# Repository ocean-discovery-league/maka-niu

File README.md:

# maka-niu

"Maka" - Eye, "Niu" - Coconut

Maka Niu, aka the "CocoCam,"  is a low-cost oceanographic camera and sensor platform that enables the exploration of undersea environments using a new pressure-tolerant camera housing and an all-natural, locally sourced, biodegradable buoyancy-control device. The coconut (Cocos nucifera ) can float for over 3,000 miles and still remain viable; as such, it makes an excellent organic platform for deploying scientific apparatus.

Maka Niu is a community-driven project that allows local groups to explore and monitor their marine resources. Based around off-the-shelf single-board computers and readily available microprocessors, Maka Niu is inexpensive to produce, easy to program, and simple to use. Designed as an open platform for scientific education and exploration, it will give classrooms and communities the ability to upload video and sensor data into FathomNet, a centralized database where machine learning algorithms assist with classification of marine species, seabed substrate identification, and accumulated time-series sensor data. This data will be publically available, allowing visualization, sharing, and discussion with policy makers from the local to global levels.

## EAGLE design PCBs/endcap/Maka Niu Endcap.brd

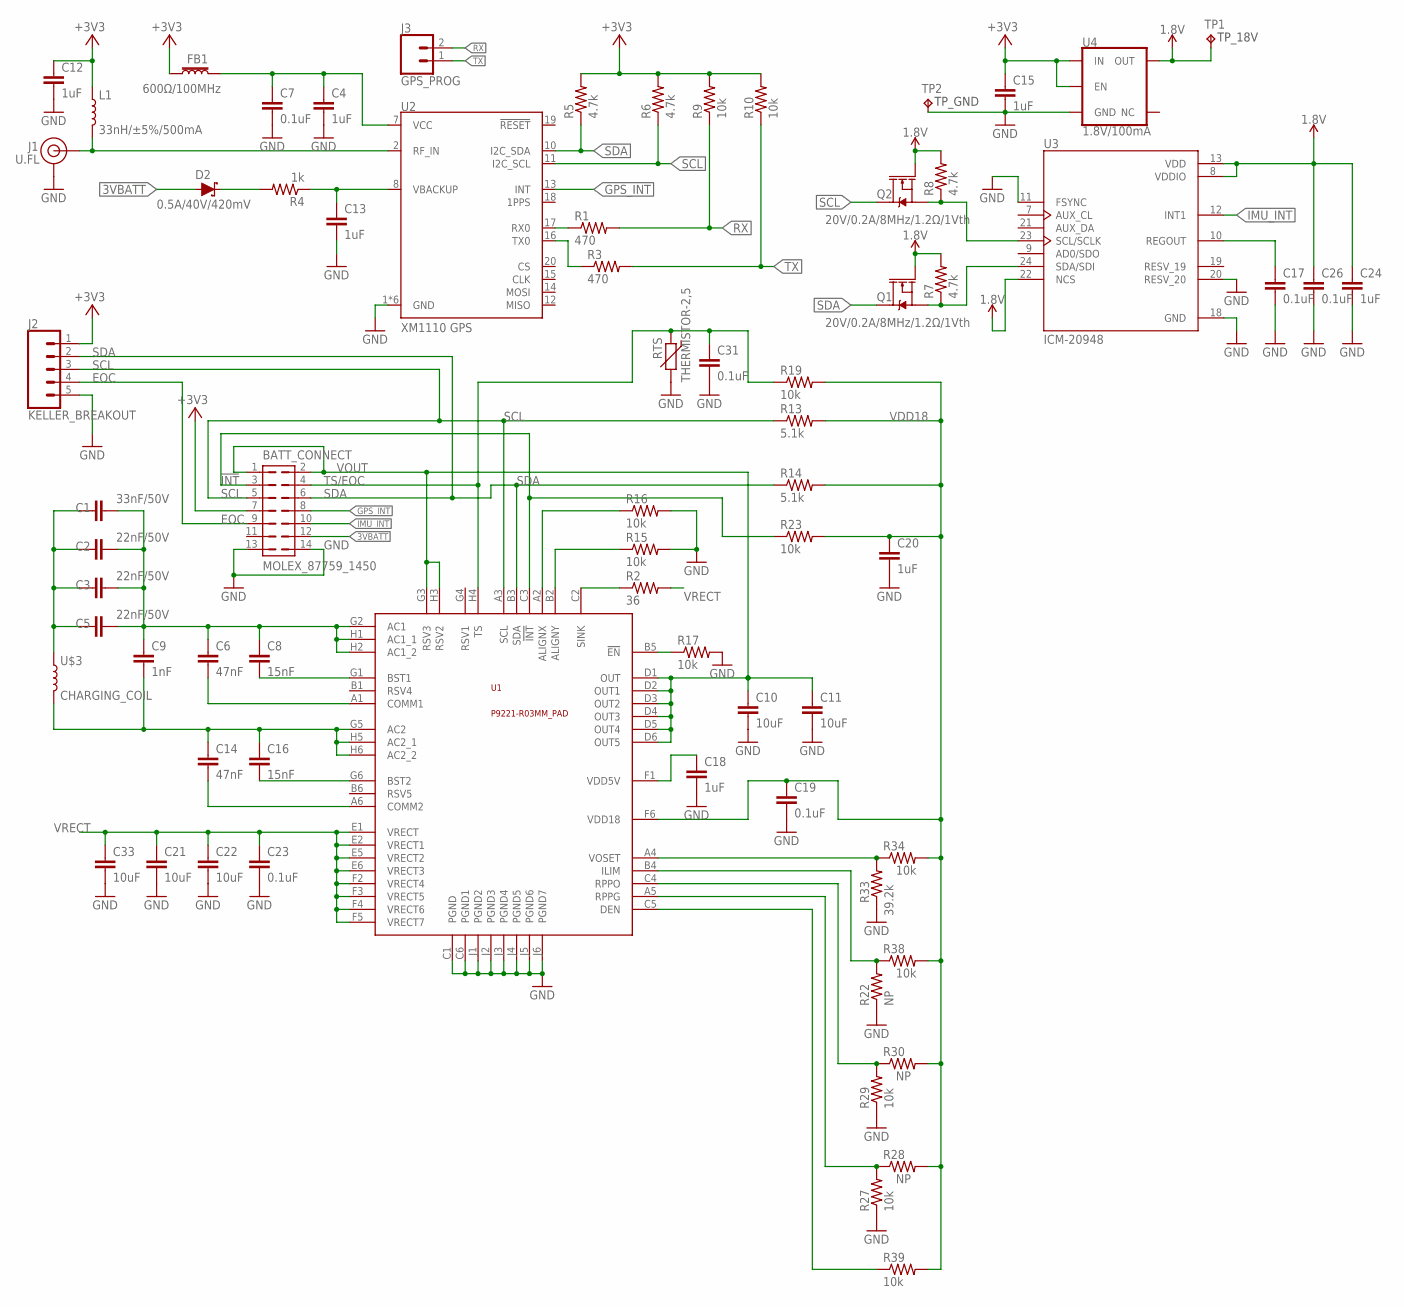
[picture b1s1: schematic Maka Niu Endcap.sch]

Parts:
BATT_CONNECT: MOLEX_87759_1450; 87759-1450; DIGI-KEY_PART_NUMBER WM18654-ND
C1: 33nF/50V; C0402; DIGI-KEY_PART_NUMBER 490-13296-1-ND
C2, C3, C5: 22nF/50V; C0402; DIGI-KEY_PART_NUMBER 490-6360-1-ND
C4, C12, C13, C15, C18, C20, C24: 1uF; C0402; DIGI-KEY_PART_NUMBER 311-1439-1-ND
C6, C14: 47nF; C0402; DIGI-KEY_PART_NUMBER 490-10702-1-ND
C7, C17, C26: 0.1uF; C0402; DIGI-KEY_PART_NUMBER 490-11917-1-ND
C8, C16: 15nF; C0402; DIGI-KEY_PART_NUMBER 490-16428-1-ND
C9: 1nF; C0402; DIGI-KEY_PART_NUMBER 732-7556-1-ND
C10, C11, C21, C22, C33: 10uF; C_0603; DIGI-KEY_PART_NUMBER 445-9015-1-ND
C19, C31: 0.1uF; C0201; DIGI-KEY_PART_NUMBER 445-7318-1-ND
C23: 0.1uF; C0201; DIGI-KEY_PART_NUMBER 1276-1318-1-ND
D2: 0.5A/40V/420mV; SOD-323; DIGI-KEY_PART_NUMBER 1727-5209-1-ND
FB1: 600Ω/100MHz; 0603; DIGI-KEY_PART_NUMBER 445-172898-1-ND
J1: U.FL; DIGI-KEY_PART_NUMBER A144746CT-ND
J2: KELLER_BREAKOUT; WIRES_2MM_05
J3: GPS_PROG; WIRES_2MM_02SMD
L1: 33nH/±5%/500mA; 0603; DIGI-KEY_PART_NUMBER 490-14837-1-ND
Q1, Q2: 20V/0.2A/8MHz/1.2Ω/1Vth; SOT-416FL; DIGI-KEY_PART_NUMBER RE1C002UNTCLCT-ND
R1, R3: 470; R0402; DIGI-KEY_PART_NUMBER RMCF0402JT470RCT-ND
R2: 36; R0805; DIGI-KEY_PART_NUMBER P36ADCT-ND
R4: 1k; R0402; DIGI-KEY_PART_NUMBER RMCF0402JT1K00CT-ND
R5, R6, R7, R8: 4.7k; R0402; DIGI-KEY_PART_NUMBER RMCF0402JT4K70CT-ND
R9, R10: 10k; R0402; DIGI-KEY_PART_NUMBER RMCF0402JT10K0CT-ND
R13, R14: 5.1k; R0402; DIGI-KEY_PART_NUMBER CR0402-JW-512GLFCT-ND
R15, R16: 10k; R_0603; DIGI-KEY_PART_NUMBER 311-10.0KHRCT-ND
R17, R19, R23, R27, R29, R34, R38, R39: 10k; R0402; DIGI-KEY_PART_NUMBER 541-10KATCT-ND
R22, R28, R30: NP; R0402
R33: 39.2k; R0402; DIGI-KEY_PART_NUMBER 311-39.2KLBCT-ND
RTS: THERMISTOR-2,5; RS-2,5
TP1: TP_18V; B1,27
TP2: TP_GND; B1,27
U1: P9221-R03MM_PAD; CSP52_2P64X3P94_0P4MM_03MMPAD; DIGI-KEY_PART_NUMBER 800-3932-2-ND
U2: XM1110 GPS; XM1110_GPS; DIGI-KEY_PART_NUMBER 1645-XM1110_1104311CT-ND
U3: ICM-20948; QFN40P300X300X105-24N
U4: 1.8V/100mA; SC70; DIGI-KEY_PART_NUMBER 576-2807-1-ND
U$3: CHARGING_COIL

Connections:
1.8V: C24.1, C26.1, Q1.1 (G), Q2.1 (G), R7.2, R8.2, TP1.TP, U3.8 (VDDIO), U3.13 (VDD), U3.22 (NCS), U4.5 (OUT)
3VBATT: BATT_CONNECT.12, D2.A
!INT: BATT_CONNECT.3, R23.1, U1.C3 (!INT)
+3V3: BATT_CONNECT.7, C12.1, C15.1, FB1.1, J2.1, L1.1, R5.2, R6.2, R9.2, R10.2, U4.1 (IN), U4.3 (EN)
AC1: C1.2, C2.2, C3.2, C5.2, C6.1, C8.1, C9.1, U1.G2 (AC1), U1.H1 (AC1_1), U1.H2 (AC1_2)
AC2: C9.2, C14.1, C16.1, U1.G5 (AC2), U1.H5 (AC2_1), U1.H6 (AC2_2), U$3.B2 (2); also elsewhere on the board
ALIGNX: R16.1, U1.A2 (ALIGNX)
ALIGNY: R15.1, U1.B2 (ALIGNY)
BST1: C8.2, U1.G1 (BST1)
BST2: C16.2, U1.G6 (BST2)
COMM1: C6.2, U1.A1 (COMM1)
COMM2: C14.2, U1.A6 (COMM2)
DEN: R39.1, U1.C5 (DEN)
EOC: BATT_CONNECT.9, J2.4
GND: BATT_CONNECT.13, BATT_CONNECT.14, C4.2, C7.2, C10.2, C11.2, C12.2, C13.2, C15.2, C17.2, C18.2, C19.2, C20.2, C21.2, C22.2, C23.2, C24.2, C26.2, C31.2, C33.2, J1.1 (GND), J1.2 (GND), J2.5, R15.2, R16.2, R17.2, R22.1, R27.1, R29.1, R33.1, RTS.2, TP2.TP, U1.C1 (PGND), U1.C6 (PGND1), U1.J1 (PGND2), U1.J2 (PGND3), U1.J3 (PGND4), U1.J4 (PGND5), U1.J5 (PGND6), U1.J6 (PGND7), U2.1 (GND), U2.3 (GND), U2.4 (GND), U2.5 (GND), U2.6 (GND), U2.9 (GND), U3.11 (FSYNC), U3.18 (GND), U3.20 (RESV_20), U4.2 (GND)
GPS_INT: BATT_CONNECT.8, U2.13 (INT)
ILIM: R22.2, R38.1, U1.B4 (ILIM)
IMU_INT: BATT_CONNECT.10, U3.12 (INT1)
LC: C1.1, C2.1, C3.1, C5.1, U$3.B1 (1); also elsewhere on the board
unnamed: R17.1, U1.B5 (!EN)
unnamed: D2.C, R4.2
REGOUT: C17.1, U3.10 (REGOUT)
RF_IN: J1.FEED (SIGNAL), L1.2, U2.2 (RF_IN)
RPPG: R27.2, R28.1, U1.A5 (RPPG)
RPPO: R29.2, R30.1, U1.C4 (RPPO)
RX: J3.2, R1.2, R9.1
RX0: R1.1, U2.17 (RX0)
SCL: BATT_CONNECT.5, J2.3, Q2.3 (D), R6.1, R13.1, U1.A3 (SCL), U2.11 (I2C_SCL)
SCL/SCLK: Q2.2 (S), R8.1, U3.23 (SCL/SCLK)
SDA: BATT_CONNECT.6, J2.2, Q1.3 (D), R5.1, R14.1, U1.B3 (SDA), U2.10 (I2C_SDA)
SDA/SDI: Q1.2 (S), R7.1, U3.24 (SDA/SDI)
SINK: R2.1, U1.C2 (SINK)
TS/EOC: BATT_CONNECT.4, C31.1, R19.1, RTS.1, U1.H4 (TS)
TX: J3.1, R3.2, R10.1
TX0: R3.1, U2.16 (TX0)
VBACKUP: C13.1, R4.1, U2.8 (VBACKUP)
VCC: C4.1, C7.1, FB1.2, U2.7 (VCC)
VDD5V: C18.1, U1.F1 (VDD5V)
VDD18: C19.1, C20.1, R13.2, R14.2, R19.2, R23.2, R28.2, R30.2, R34.2, R38.2, R39.2, U1.F6 (VDD18)
VOSET: R33.2, R34.1, U1.A4 (VOSET)
VOUT: BATT_CONNECT.1, BATT_CONNECT.2, C10.1, C11.1, U1.D1 (OUT), U1.D2 (OUT1), U1.D3 (OUT2), U1.D4 (OUT3), U1.D5 (OUT4), U1.D6 (OUT5), U1.G3 (RSV3), U1.H3 (RSV2)
VRECT: C21.1, C22.1, C23.1, C33.1, R2.2, U1.E1 (VRECT), U1.E2 (VRECT1), U1.E5 (VRECT2), U1.E6 (VRECT3), U1.F2 (VRECT4), U1.F3 (VRECT5), U1.F4 (VRECT6), U1.F5 (VRECT7)

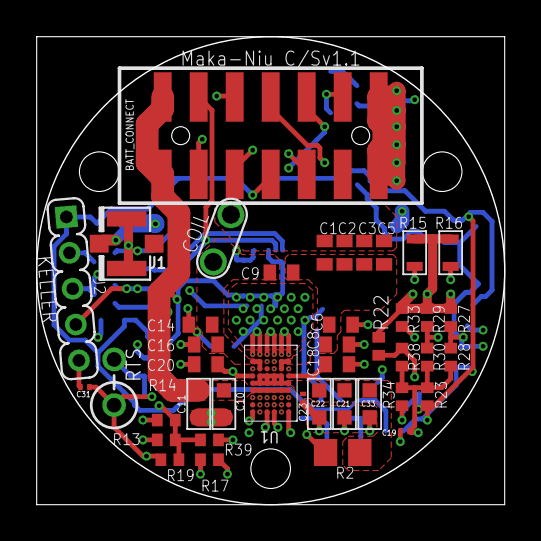
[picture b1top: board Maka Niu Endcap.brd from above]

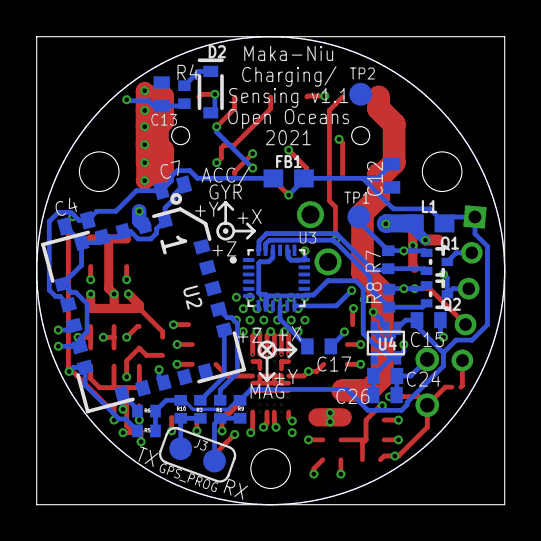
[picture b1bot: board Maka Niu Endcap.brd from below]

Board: 6 copper layers, 26.0 x 26.0 mm, 70 parts (28 on the bottom side), 42 nets.

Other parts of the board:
COIL: CHARGING_COIL

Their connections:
AC2: COIL.B2; also elsewhere on the board
LC: COIL.B1; also elsewhere on the board

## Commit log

2020-06-24 Lui's first commit, addign a python script to record video on the Pi Zero with aa camera module, with timestamp overlay. This could be used in Maka Niu to overlay temperature, depth etc. Also adding 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
2020-06-24 reorganized directory for future use
2020-07-07 Add files via upload
    Uploads a specified file to Tator
2020-07-07 Add files via upload
    Bash file to upload all mp4 files in directory (Calls TatorUpload.py with given arguments)
2020-07-13 added the kellerLD library, and a version of the example with a depth estimation based on pressure.
2020-07-17 Added a more complex python program Mode_dial_with_button for testing the the new hall sensor ring togethr with the new dial lthat incorporates a button
2020-07-31 added XM1110_example.py and supporting library. Example gets NMEA data from XM1111 via I2C and updates class objects with relevant info.
2020-08-13 Added the hall ring magnetic dial Kicad project
2020-08-13 added the battery management board kicad project
2020-08-13 Icreased trace thickness and rerouted higher freq and power paths in the battery management board
2020-08-14 added documenation folder and pushed 1st Power Distribution Chart
2020-08-14 Updated index.php: can access program.php, upload w button
2020-08-14 Updated index.php w program.php link and upload button
2020-08-14 Scaffold of page for user programmed missions
2020-08-14 added the maka niu general build BOM, and the maka niu build guide
2020-08-14 Chart of the code for program.php
    Displays all of the possible code blocks user would want to create and the respective strings for use in translating into python, and the string used to display html components
2020-08-14 changed current sensing resistor values on the BMS board to appropriately trip short and over current situations, adn to appropriately end incomig charge
2020-08-18 assigned digikey part to every item in battery management schematic, and created BOM
2020-08-31 Add files via upload
    Visual Representation and estimation calculation
2020-08-31 Add files via upload
    Documentation for Visual Representation and estimation calculations
2020-09-03 adding in progress pcb design files for the charging Station
2020-09-22 completed the wireless charger PCB design as rev 0. bom is compiled
2020-09-25 minor updating on BOM organization
2020-09-25 safety merge
2020-10-02 adding LED patterns simplified.
2020-10-22 first attempt at adding RPiCWI as a submodule
2020-10-23 added makaniu BMS board V2, and wayfinders 6cell BMS.
2020-11-22 Added haptic feedback to the Mode Dial python script
2020-11-22 updates to battery managemennt wayfinder boards, and makaniu hall sensor ring and BMS
2020-11-23 Fine of haptic feedback. new click, double click, burst, and dial change incorporated
2020-11-23 bit more fine tuning on haptic feedback. The clicks are nicer, but too hard notice by feel. Hearing them gives the illusion that they are enough, but with noise canceling headphones on, I can barely 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
2020-12-04 added comments for GPIOS
2020-12-04 Minor notes on BMS pcb project
2020-12-04 added Maka Niu User Flowchart.pdf in documentation
2020-12-07 Added a program called MakaNiu.py that begins to pull and incroporate all the peripheral hardware. Mode and button control, GPS, and image and video capture all working
2021-01-15 commented out drv vibration code because it causes crash if device not present
2021-01-18 MakaNiu.py program updated to include pressure info, as well as battery info, although it is disabled due to instability
2021-01-18 Lengthened update time for GPS and pressure to once every ten seconds, so that it interferes less with button presses. Need to bring in threads maybe, thou mixing I2c is scary. Also added a program t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
2021-01-18 improved timing interference between buttons and all the i2c time
2021-01-18 added a shell script to run python program with error log
2021-01-21 added try format to keller i2c comms to avoid occasional crash.
2021-01-22 All interfaces now protected with try/except method to prevent crashes. Program will run if any of these are missing. If all is present and talking, at startup, a green LED will hold for 3 seconds. A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
2021-01-22 added crash protection on DRV haptic feedback i2c. now Pi runs even if no interface connected.
2021-01-22 added the error log save destination on git
2021-01-25 Due to a a sepcific startup issue that emerged with introduciton of spi1, the shutdown pin has been switched with the enable endcap pin. Also added the enable endcap feature.
2021-01-26 added green light flash for GPS fix
2021-02-02 Incorporated date time from GPS. Required some changes in the gps libraries.
2021-02-02 Add files via upload
    Silkscreen modified for production
2021-02-02 Add files via upload
    Updated silkscreens
2021-02-02 Add files via upload
    Finalized for production
2021-02-02 Add files via upload
    added documentation for endcap PCB
2021-02-02 incorporated ability to name image files
2021-02-04 sped up shut down sequence
2021-02-05 added crash prptection with try for gps data
2021-02-05 added Pi video file naming, and added serial number to img and video naming.
2021-02-12 added sensor data file creation for videos
2021-02-12 heavy addition and cleanup of comments
2021-02-13 added creation of data file in missions
2021-02-13 added sensor data saving for images and burst images. Addressed a bug where burst photos also start a video.
2021-02-15 Added system clock entry in the sensor data files so that the separate mission manager program can easily read entry time
2021-02-17 implemented rotating data and error logging
2021-02-18 Added IMU sensor data collection and write to sensor files
2021-02-19 added battery power indication in wifi mode when battery pressed
2021-02-22 added use of pi os hostname in filenaming
2021-02-22 removed import of makaniu_config.py for now, not currently used
2021-02-22 sensor file writing now has has flush built into every print to update the files faster, and mode changes are written to a status file in log directory for easy read by other running software
2021-02-23 software/hardware fix of imu address bug. pin address was floating in hardware, so hardware fix sets the address to 0x69. Software follows the correction
2021-02-24 fixed datestamp for special case gns2 data in photo captures
2021-02-25 updated the repo with all latest pcb changes for the 6cell bms, 3cell bms, and for the wireless charger. Also added sensor data readme filein the same directory as the makaniu python program
2021-04-04 disabled led and hdmi cuttoff after some time, till this feature is really needed feo deployment
2021-04-08 added device id and mac address data to the top of each generated sensor file
2021-05-17 converted to non-dos eols, flush stdout on upload progress reports
2021-05-21 hacked in support for uploading attachments
2021-05-21 added link to attachments upload tutorial
2021-05-25 upload to folder named by hostname
2021-05-26 Reinstated LED and HDMI shutdown for poer saving, and reduced burst photo rate to 2hz to sidestep a bug that caused missing thumbnail images
2021-07-08 implemented keller depth offset background calibration that uses gps fix as reference for 0 depth.
2021-07-08 implemented clock update from gps even without a fix. Also disabled wifi in non wifi modes for power saving
2021-11-17 created a script locker folder to hold code that needs to be manually copied to other places. Also upgraded the wifi disbale code to close the access point.
2021-11-17 code version print changed to 1.03, to make it a little easier to track if users are up to date
2021-12-10 added a dimmensioned drawing of the Maka Niu Housing in the documentation section
2021-12-11 minor correction to a dimenisions pdf drawing of the enclosure
2021-12-17 correction to dimensioned diagram
2022-01-22 added a more files to the script_locker of code that needs to copied to directories outside the git project
2022-01-29 makaniu.py has minor edits. big one is keeping wifi enabled in non wifi mode if camera is believed to be above water
2022-02-01 removed outdated battery manager schematic
2022-02-01 changed voltage ranges for feedback so that the full charge 5 flashes are more likely to show on a full charge
2022-02-02 revised battery level visual feedback threshold voltages again based on observed voltage over time for a full charge to full deplete mission
2022-02-03 rc.local in the scriptlocker made smarter. Now errors are appended to the error log, so that they can be reviewed in perpetuity
2022-02-14 implemeted basic verion printing with incremented commits
2022-02-14 corrected bug on version printing when the daemon is called from outside the git repo, such as on boot
2022-02-18 removed annotation over images and video by RPI cam interface
2022-04-25 check files by filename and skip uploading duplicate, switch to makaniu uploads account API token
2022-04-25 moved the TatorUpload.py script into the coconut repo
2022-06-15 added new pcb projects: hall_ring, pi_zero_shield, and batter_manager_V1.1
2022-07-05 number of PCBs for 2nd round of Maka Niu fabrication, in their state after orders made.
2022-07-07 added a code sample for a great passive buzzer controller
2022-07-17 changes to MakaNiu to make it resilient to bad keller offset value on start up. Also slight change to how the ofset is calucalted, by adding the variable uncalibrated depth.
2022-07-29 added beginnig of MakaNiu LED ligth code with quality PWM control
2022-07-30 got MakaLED to work with the dial
2022-07-30 minor change to auto_copy_scripts so create startstop.sh next to startstopX.sh. Reason: pi interfaces seems to randomly revert back to startstop.sh, so we shouldnt use the X name anymore.
2022-08-05 added battery reading to MakaLED.py
2022-08-05 added battery level coutn in wifi button press for the flashlight code
2022-09-21 added a test python script for client side bluetooth
2022-09-21 added python script for testing bluetooth host side
2022-09-23 added the GNS2 line for videos. Till now, it was only given for images.
2022-10-25 added bluettooth LED module code. Still testing
2022-11-12 Changes to MakaNiu.py to accomodate new hardware, while still hopefully working on old hardware.
2022-11-19 more work on new hardware compatibility. Scripts added to setup units for either
2022-11-19 corrected IP address for LED version
2023-01-16 changed audio frequency to be audible outside of housing
2023-01-19 added method for Maka Niu to control LED module over bluetooth. An initial connection between two units must still be done manually over command line once, but afterwards units can be rebooted and th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
2023-01-19 cleaned up the LED module code quite a bit, removing some undefined/unusued variables, making it much more stable
2023-01-19 changed the trigger to attempt bluetooth connection to when getting batterly level. More user friendly
2023-01-19 revised how to retrieve bluetooth device name and address to. It now gets it diretly from the bluetooth hardware, rather than from a manual text file
2023-01-26 deleted the PCBs folder from the maka-niu project. That content has been moved to maka-ni-design-files project.
2023-02-01 a test branch created to easily disable the beep on Maka Niu units
2023-02-01 completely disabled pigpiod
2023-02-04 extended the no_beep branch to also not do haptic feedback. Testing if the haptic driver is somehow the issue for unit 0018, which seems to chrash, especially during photo burst

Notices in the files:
parts and their libraries:
SparkFun-DiscreteSemi: Licensing: Creative Commons ShareAlike 4.0 International - https://creativecommons.org/licenses/by-sa/4.0
